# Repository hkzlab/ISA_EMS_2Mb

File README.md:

# ISA 2Mb EMS Expansion

## Introduction

This is a reimplementation of the **lo-tech.co.uk** [2Mb ISA EMS board](https://www.lo-tech.co.uk/wiki/Lo-tech_2MB_EMS_Board) with the following changes:

- All thru-hole instead of SMD, while retaining a rather compact format
- Activity led to indicate when the memory is accessed

### Disclaimer

I take NO responsibility for what happens if you decide to build and use this card. Your computer might crash, catch fire or be destroyed in other nasty ways.
Also, as this card is mostly based on the work of others, You're encourauged to take what you deem fit from this, and use it in your projects!

Additionally, do **NOT CONTACT lo-tech.co.uk FOR SUPPORT**, while this board is derived from their work, it is not their product, please do not waste their time.

## Configuration

### EMS

To configure the EMS, jumpers on J2 header are used.

Pins 1 and 2 configure the Page Frame base address, while 3 and 4 configure the IO Port base address.

```text

EMS Page Frame Base
 1 | 2 | Base  |
---+---+-------+
 X | X | C000h |
---+---+-------+
   | X | D000h |
---+---+-------+
 X |   | E000h |
---+---+-------+
   |   | Inval |
---+---+-------+

EMS IO Port Base
 3 | 4 |   Base     |
---+---+------------+
 X | X |  260-263h  |
---+---+------------+
   | X |  264-267h  |
---+---+------------+
 X |   |  268-26Bh  |
---+---+------------+
   |   |  26C-26Fh  |
---+---+------------+

```

## Usage

You need a **memory manager** to use this board. I'm including the `LTEMM` driver provided by lo-tech in this repository. Please refer to [this](https://www.lo-tech.co.uk/wiki/Terms_and_Conditions) page regarding the terms of use.

## Bill of Materials

All ICs are in DIP package.

- U7, U8: 74HCT688
- U3, U4, U5, U6: AS6C4008 (You don't need to fill all sockets: fit as much memory as you need starting from socket 1!)
- U11: 74HC04 (HCT is fine too)
- U9: 74HCT139
- U10: 74HCT32
- U12: 74LS245 (You can substitude this for an HCT/ACT/F/ALS part)
- U17: 74HCT138
- U18, U19, U20, U21: 74HCT573
- RN2: res. network, 10k, bussed, 5 pins
- RN3: res. network, 10k, bussed, 9 pins.
- R3: ~470-1k resistor (depends on the type of LED mounted on D1 and desired brightness)
- D1: 3.0mm or 5.0mm LED, you can use an horizontal mount led too
- J2 2x4 2.5mm breakable header
- C5, C6: 10uF / 50v electrolytic caps
- Remaining caps: 16x 100nF, ceramic
- ISA bracket: Keystone 9202, plus screws. You will have to cut a hole for the LED.

## Known Issues

I have received reports of this board being unstable when used with some homebrew PC clones, reports included the Xi8088 and NuXT. I have noted similar issues on a Micro8088. On the other hand, an all-CMOS board was tested fine on multiple AT clones I have.
Replacing the following ICs with ones from the TTL family solved the issue for me: U7, U8, U9, U10, U11, U12.

Note that, for increased stability, I use an ISA terminator with these homebrew computers.

## Credits

- Thanks to [lo-tech.co.uk](https://www.lo-tech.co.uk/) for having published their schematics
- Thanks to [Sergey](http://www.malinov.com/Home/sergeys-projects) for all his projects!

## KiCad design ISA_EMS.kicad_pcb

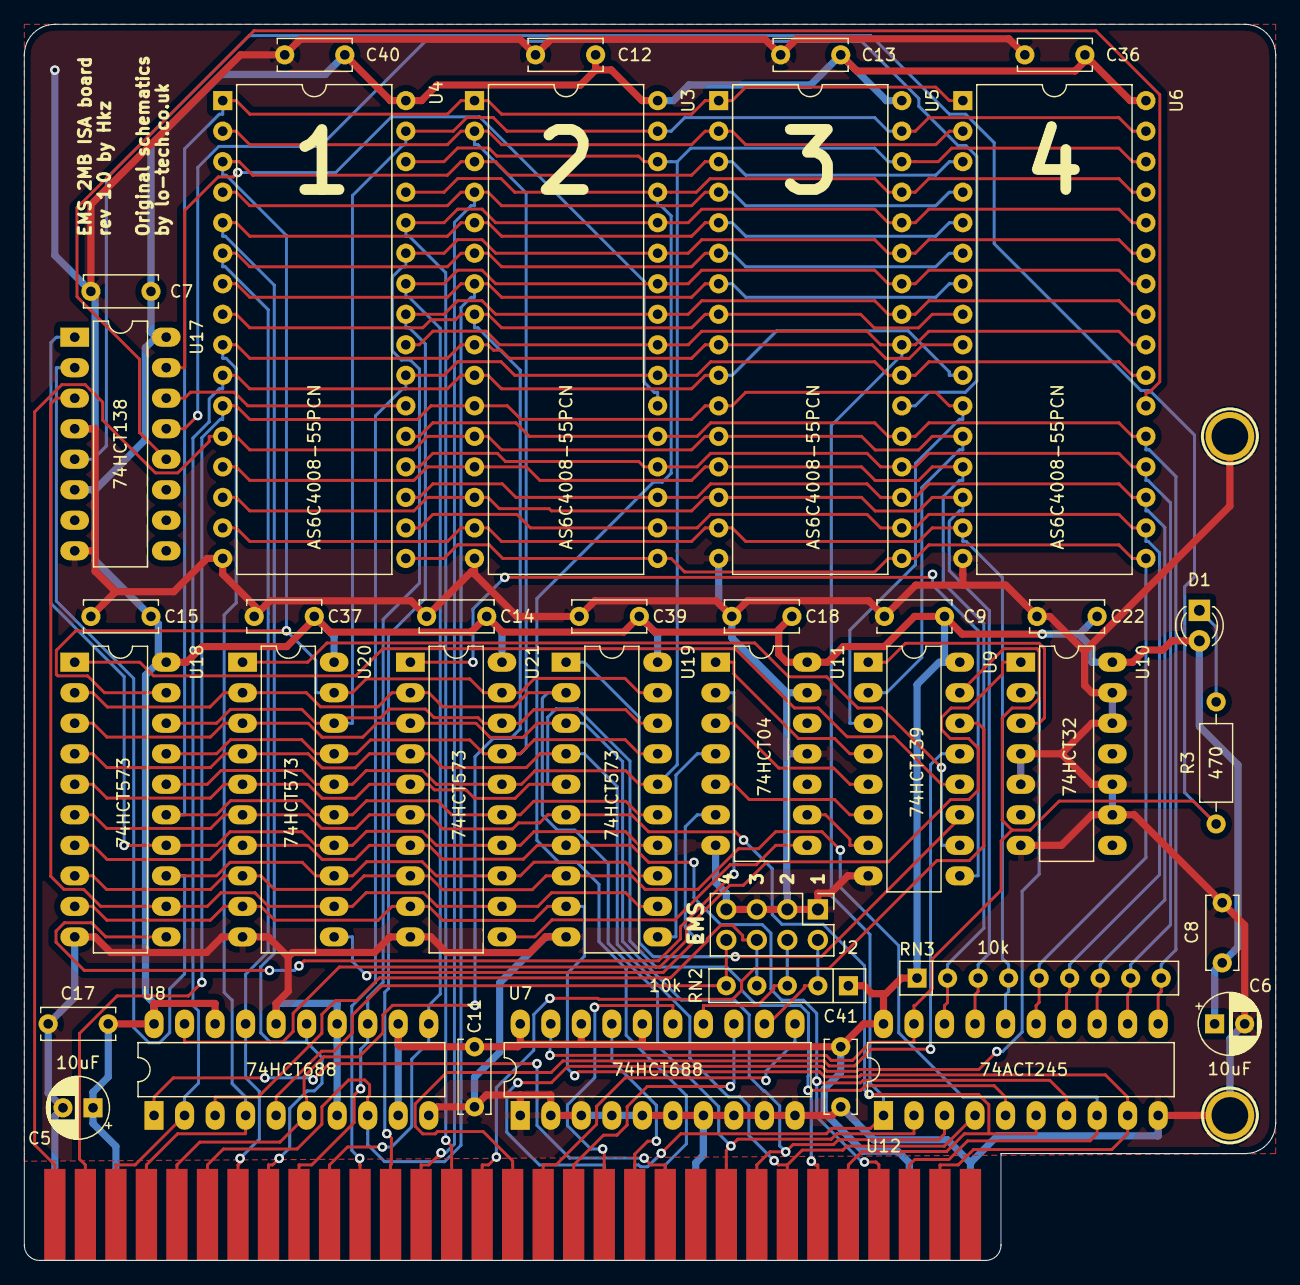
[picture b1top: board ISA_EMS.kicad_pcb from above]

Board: 2 copper layers, 104.1 x 102.9 mm, 41 parts (0 on the bottom side), 74 nets.

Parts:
C5, C6: 10uF; CP_Radial_D5.0mm_P2.50mm
C7, C8, C9, C11, C12, C13, C14, C15, C17, C18, C22, C36, C37, C39, C40, C41: 100nF; C_Disc_D6.0mm_W2.5mm_P5.00mm
D1: EMS in use; LED_D3.0mm_Clear
H1, H2: MountingHole_Pad; Hole_3mm
J1: ISA BUS; Conn_Edge_PCB_ISA8
J2: EMS Address; PinHeader_2x04_P2.54mm_Vertical
R3: 470; R_Axial_DIN0207_L6.3mm_D2.5mm_P10.16mm_Horizontal
RN2: 10k; R_Array_SIP5
RN3: 10k; R_Array_SIP9
U3, U4, U5, U6: AS6C4008-55PCN; DIP-32_W15.24mm
U7, U8: 74HCT688; DIP-20_W7.62mm_LongPads
U9: 74HCT139; DIP-16_W7.62mm_LongPads
U10: 74HCT32; DIP-14_W7.62mm_LongPads
U11: 74HCT04; DIP-14_W7.62mm_LongPads
U12: 74ACT245; DIP-20_W7.62mm_LongPads
U17: 74HCT138; DIP-16_W7.62mm_LongPads
U18, U19, U20, U21: 74HCT573; DIP-20_W7.62mm_LongPads

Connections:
/A0: J1.62, U3.12, U4.12, U5.12, U6.12, U9.2
/A1: J1.61, U3.11, U4.11, U5.11, U6.11, U9.3
/A2: J1.60, U3.10, U4.10, U5.10, U6.10, U8.2
/A3: J1.59, U3.9, U4.9, U5.9, U6.9, U8.4
/A4: J1.58, U3.8, U4.8, U5.8, U6.8, U8.6
/A5: J1.57, U3.7, U4.7, U5.7, U6.7, U8.8
/A6: J1.56, U3.6, U4.6, U5.6, U6.6, U8.17
/A7: J1.55, U3.5, U4.5, U5.5, U6.5, U8.15
/A8: J1.54, U3.27, U4.27, U5.27, U6.27, U8.13
/A9: J1.53, U3.26, U4.26, U5.26, U6.26, U8.11
/A10: J1.52, U3.23, U4.23, U5.23, U6.23
/A11: J1.51, U3.25, U4.25, U5.25, U6.25
/A12: J1.50, U3.4, U4.4, U5.4, U6.4
/A13: J1.49, U3.28, U4.28, U5.28, U6.28
/A14: J1.48, U9.14
/A15: J1.47, U9.13
/A16: J1.46, U7.11
/A17: J1.45, U7.13
/A18: J1.44, U7.15
/A19: J1.43, U7.17
/AEN: J1.42, U8.1
/D0: J1.40, U12.2, U18.2, U19.2, U20.2, U21.2
/D1: J1.39, U12.3, U18.3, U19.3, U20.3, U21.3
/D2: J1.38, U12.4, U18.4, U19.4, U20.4, U21.4
/D3: J1.37, U12.5, U18.5, U19.5, U20.5, U21.5
/D4: J1.36, U12.6, U18.6, U19.6, U20.6, U21.6
/D5: J1.35, U12.7, U18.7, U19.7, U20.7, U21.7
/D6: J1.34, U12.8, U18.8, U19.8, U20.8, U21.8
/D7: J1.33, U12.9, U18.9, U19.9, U20.9, U21.9
/DB0: RN3.2, U3.13, U4.13, U5.13, U6.13, U12.18
/DB1: RN3.3, U3.14, U4.14, U5.14, U6.14, U12.17
/DB2: RN3.4, U3.15, U4.15, U5.15, U6.15, U12.16
/DB3: RN3.5, U3.17, U4.17, U5.17, U6.17, U12.15
/DB4: RN3.6, U3.18, U4.18, U5.18, U6.18, U12.14
/DB5: RN3.7, U3.19, U4.19, U5.19, U6.19, U12.13
/DB6: RN3.8, U3.20, U4.20, U5.20, U6.20, U12.12
/DB7: RN3.9, U3.21, U4.21, U5.21, U6.21, U12.11
/JP1: J2.2, RN2.2, U7.12
/JP2: J2.4, RN2.3, U7.14
/JP3: J2.6, RN2.4, U8.3
/JP4: J2.8, RN2.5, U8.5
/RAM-A14: U3.3, U4.3, U5.3, U6.3, U18.19, U19.19, U20.19, U21.19
/RAM-A15: U3.31, U4.31, U5.31, U6.31, U18.18, U19.18, U20.18, U21.18
/RAM-A16: U3.2, U4.2, U5.2, U6.2, U18.17, U19.17, U20.17, U21.17
/RAM-A17: U3.30, U4.30, U5.30, U6.30, U18.16, U19.16, U20.16, U21.16
/RAM-A18: U3.1, U4.1, U5.1, U6.1, U18.15, U19.15, U20.15, U21.15
/RAM-A19: U17.1, U18.14, U19.14, U20.14, U21.14
/RAM-A20: U17.2, U18.13, U19.13, U20.13, U21.13
/RAM-A21: U17.3, U18.12, U19.12, U20.12, U21.12
/REG0-LOAD: U11.2, U18.11
/REG1-LOAD: U11.4, U19.11
/REG2-LOAD: U11.6, U20.11
/REG3-LOAD: U11.8, U21.11
/~IOW: J1.13, U10.2
/~MEMR: J1.12, U3.24, U4.24, U5.24, U6.24, U12.1
/~MEMW: J1.11, U3.29, U4.29, U5.29, U6.29
/~RAM-CS0: U3.22, U17.15
/~RAM-CS1: U4.22, U17.14
/~RAM-CS2: U5.22, U17.13
/~RAM-CS3: U6.22, U17.12
/~RAM-SELECT: R3.1, U7.19, U9.15, U12.19, U17.5
/~REG0-OE: U9.12, U18.1
/~REG1-OE: U9.11, U19.1
/~REG2-OE: U9.10, U20.1
/~REG3-OE: U9.9, U21.1
GND: C5.2, C6.2, C7.2, C8.2, C9.2, C11.2, C12.1, C13.2, C14.2, C15.2, C17.2, C18.2, C22.2, C36.2, C37.2, C39.2, C40.2, C41.2, H1.1, H2.1, J1.1, J1.10, J1.31, J2.1, J2.3, J2.5, J2.7, U3.16, U4.16, U5.16, U6.16, U7.1, U7.2, U7.3, U7.4, U7.5, U7.6, U7.7, U7.8, U7.9, U7.10, U8.7, U8.10, U8.14, U8.16, U9.8, U10.4, U10.5, U10.7, U10.9, U10.10, U10.12, U10.13, U11.7, U11.11, U11.13, U12.10, U17.4, U17.8, U18.10, U19.10, U20.10, U21.10
unnamed: D1.1, R3.2
unnamed: U8.19, U10.1
unnamed: U9.1, U10.3
unnamed: U9.4, U11.1
unnamed: U9.5, U11.3
unnamed: U9.6, U11.5
unnamed: U9.7, U11.9
VCC: C5.1, C6.1, C7.1, C8.1, C9.1, C11.1, C12.2, C13.1, C14.1, C15.1, C17.1, C18.1, C22.1, C36.1, C37.1, C39.1, C40.1, C41.1, D1.2, J1.3, J1.29, RN2.1, RN3.1, U3.32, U4.32, U5.32, U6.32, U7.16, U7.18, U7.20, U8.9, U8.12, U8.18, U8.20, U9.16, U10.14, U11.14, U12.20, U17.6, U17.16, U18.20, U19.20, U20.20, U21.20

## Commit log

2021-04-13 Begin removing useless components
2021-04-13 Begin moving components
2021-04-14 moved components on card
2021-04-14 Add silkscreen
2021-04-14 add via to board and refill
2021-04-14 Regenerate gerbers
2021-04-15 move led slightly backward
2021-05-11 Updated README, added software
2021-11-09 Update Kicad url
2022-11-08 Update the README, add Known Issues, fix the BoM
